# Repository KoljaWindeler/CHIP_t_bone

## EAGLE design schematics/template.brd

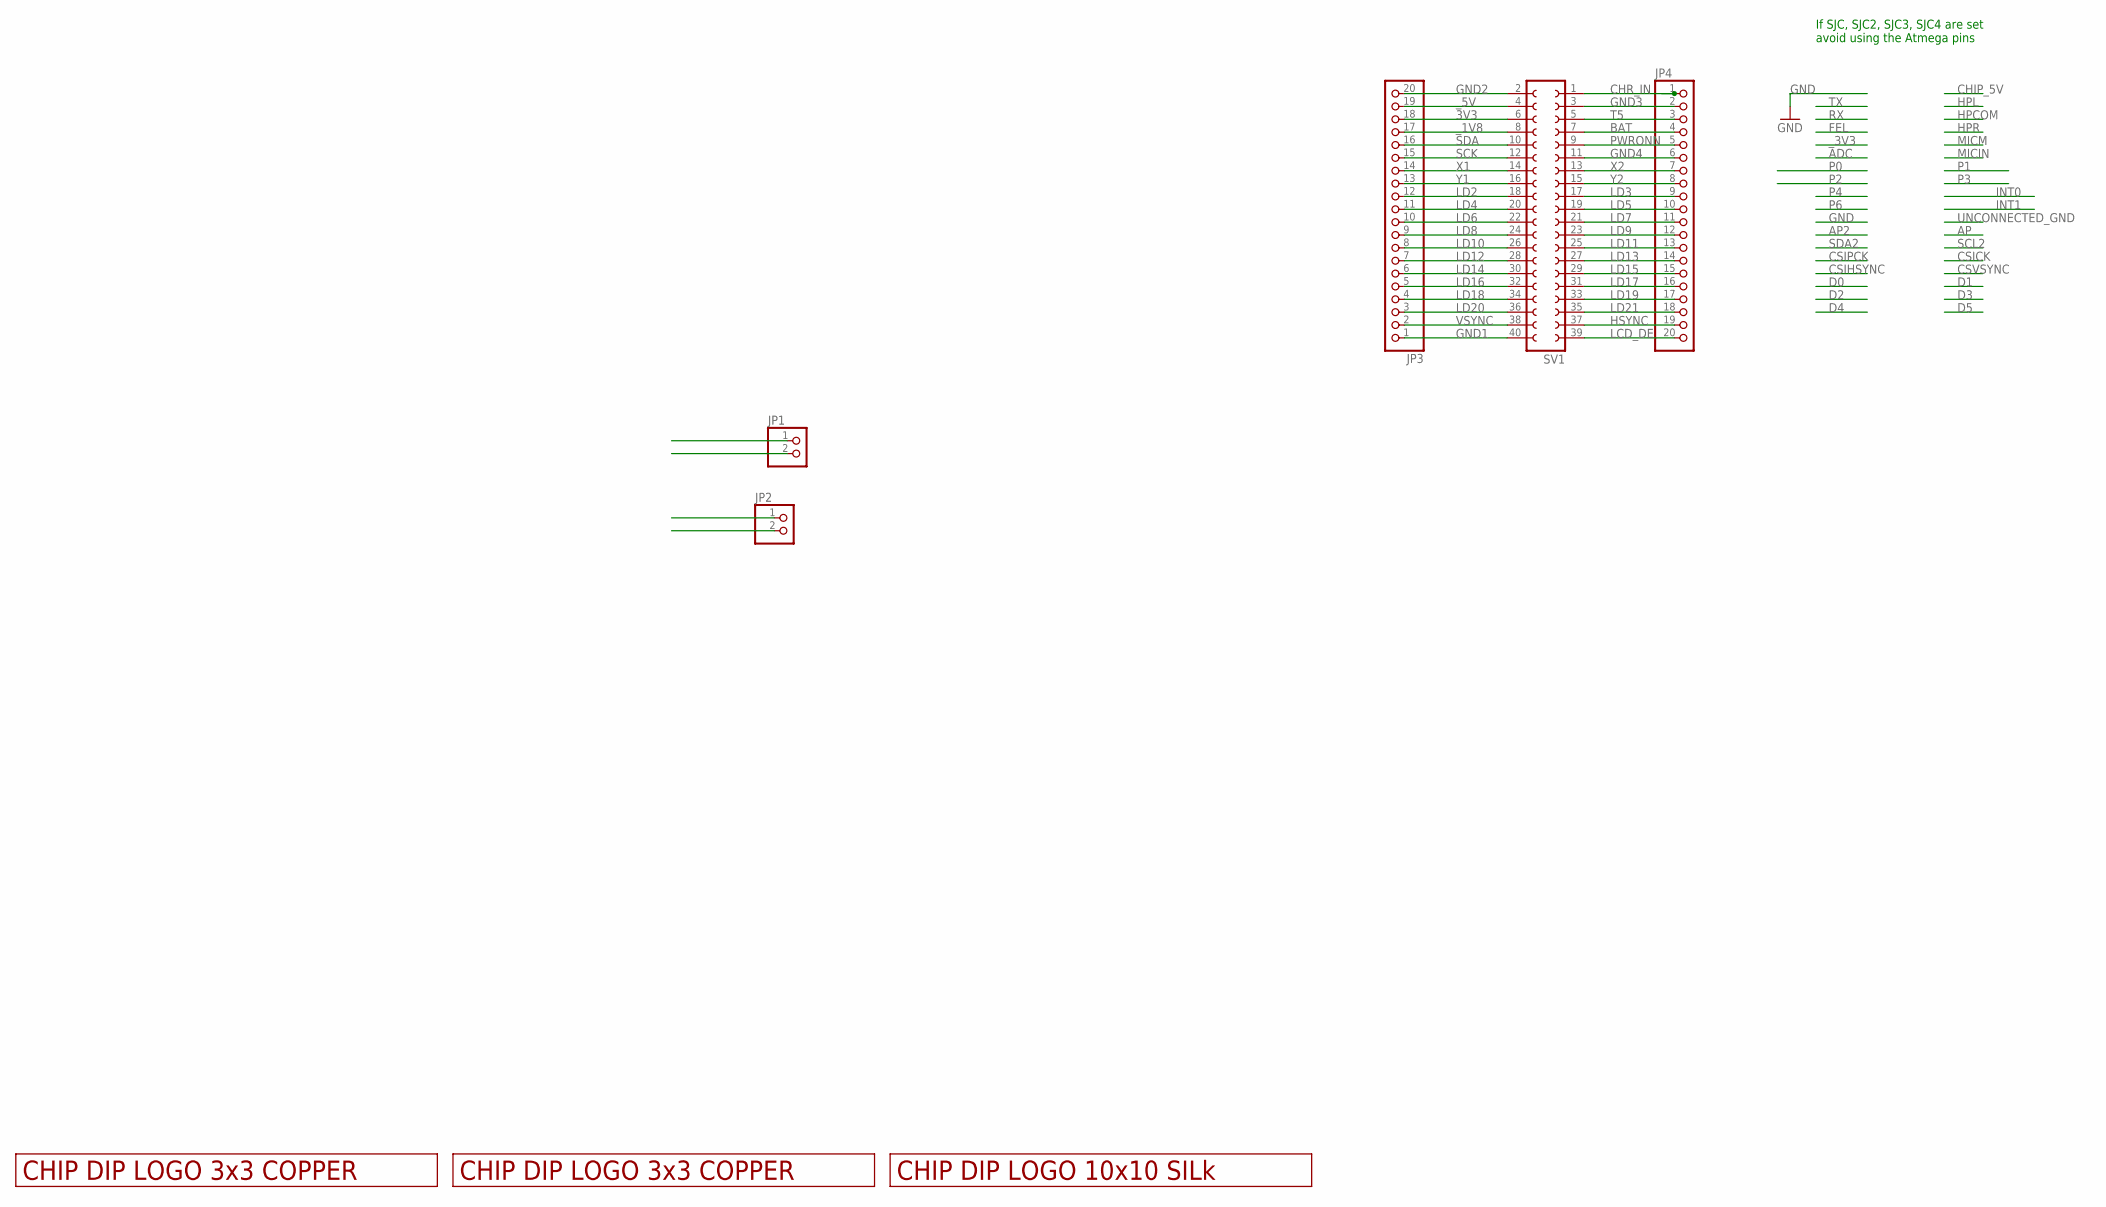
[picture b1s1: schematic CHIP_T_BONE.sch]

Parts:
JP1, JP2: PINHD-1X2; 1X02
JP3, JP4: PINHD-1X20; 1X20
SV1: FE20-2
U$2, U$4: LOGO_3X3_COPPER
U$5: LOGO_10X10_SILK

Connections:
3V3: JP2.2, JP3.18, SV1.6
BAT: JP4.4, SV1.7
CHR_IN: JP1.1, JP4.1, SV1.1
GND1: JP3.1, SV1.40
GND2: JP1.2, JP3.20, SV1.2
GND3: JP2.1, JP4.2, SV1.3
GND4: JP4.6, SV1.11
HSYNC: JP4.19, SV1.37
LCD_DE: JP4.20, SV1.39
LD2: JP3.12, SV1.18
LD3: JP4.9, SV1.17
LD4: JP3.11, SV1.20
LD5: JP4.10, SV1.19
LD6: JP3.10, SV1.22
LD7: JP4.11, SV1.21
LD8: JP3.9, SV1.24
LD9: JP4.12, SV1.23
LD10: JP3.8, SV1.26
LD11: JP4.13, SV1.25
LD12: JP3.7, SV1.28
LD13: JP4.14, SV1.27
LD14: JP3.6, SV1.30
LD15: JP4.15, SV1.29
LD16: JP3.5, SV1.32
LD17: JP4.16, SV1.31
LD18: JP3.4, SV1.34
LD19: JP4.17, SV1.33
LD20: JP3.3, SV1.36
LD21: JP4.18, SV1.35
PWRONN: JP4.5, SV1.9
SCK: JP3.15, SV1.12
SDA: JP3.16, SV1.10
T5: JP4.3, SV1.5
VSYNC: JP3.2, SV1.38
X1: JP3.14, SV1.14
X2: JP4.7, SV1.13
Y1: JP3.13, SV1.16
Y2: JP4.8, SV1.15
_1V8: JP3.17, SV1.8
_5V: JP3.19, SV1.4

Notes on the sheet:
If SJC, SJC2, SJC3, SJC4 are set avoid using the Atmega pins

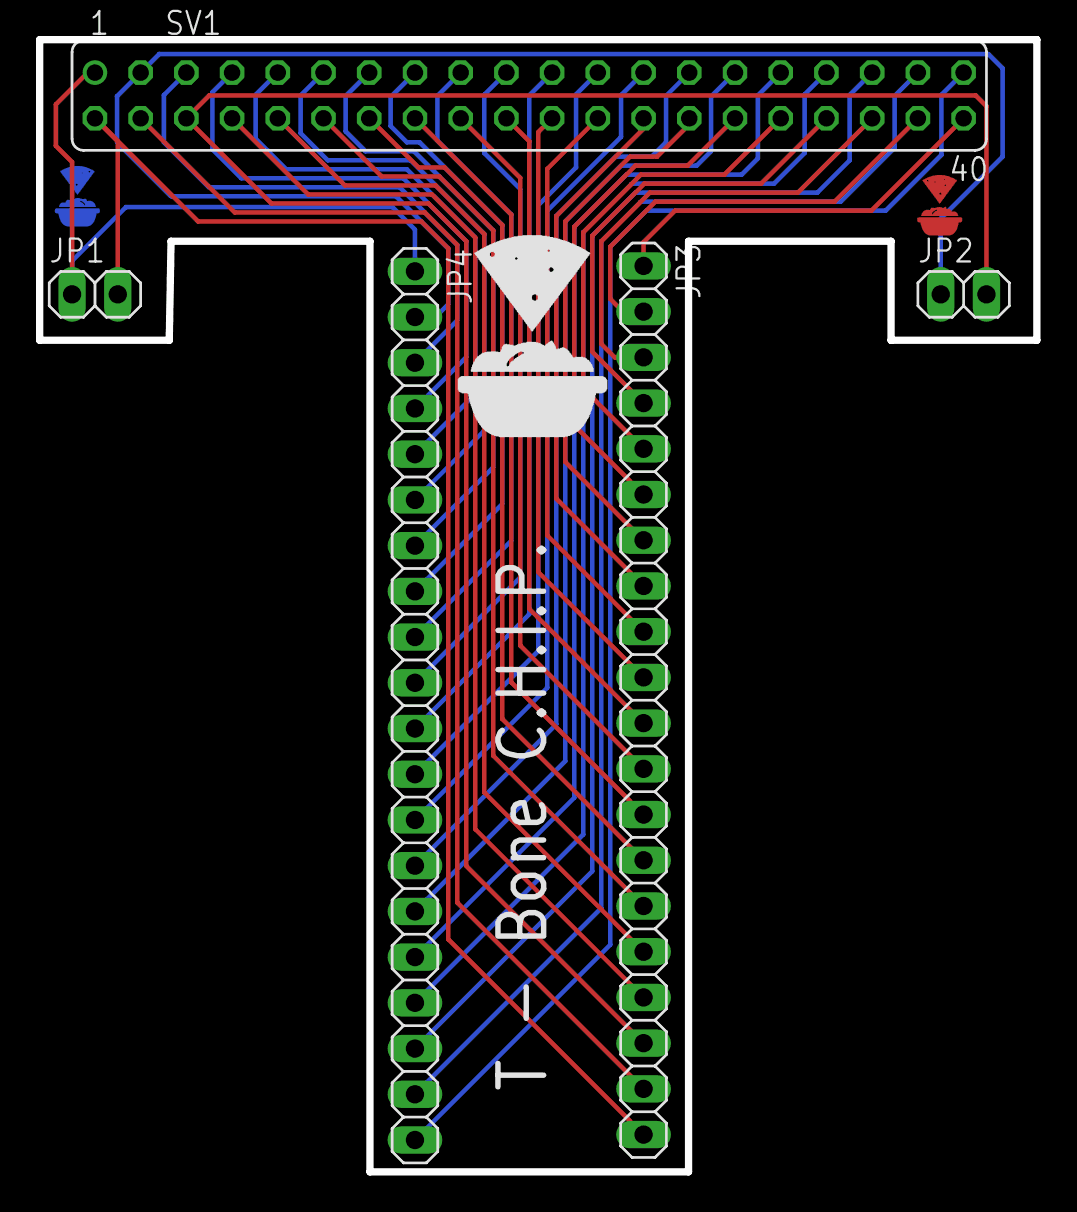
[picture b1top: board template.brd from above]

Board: 2 copper layers, 55.4 x 62.9 mm, 8 parts (1 on the bottom side), 40 nets.

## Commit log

2016-05-03 init
2016-08-20 moved files to correct folder
